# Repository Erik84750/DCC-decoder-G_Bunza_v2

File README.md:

# DCC-decoder-G_Bunza_v2
DCC++ decoder based on the work of G. Bunza

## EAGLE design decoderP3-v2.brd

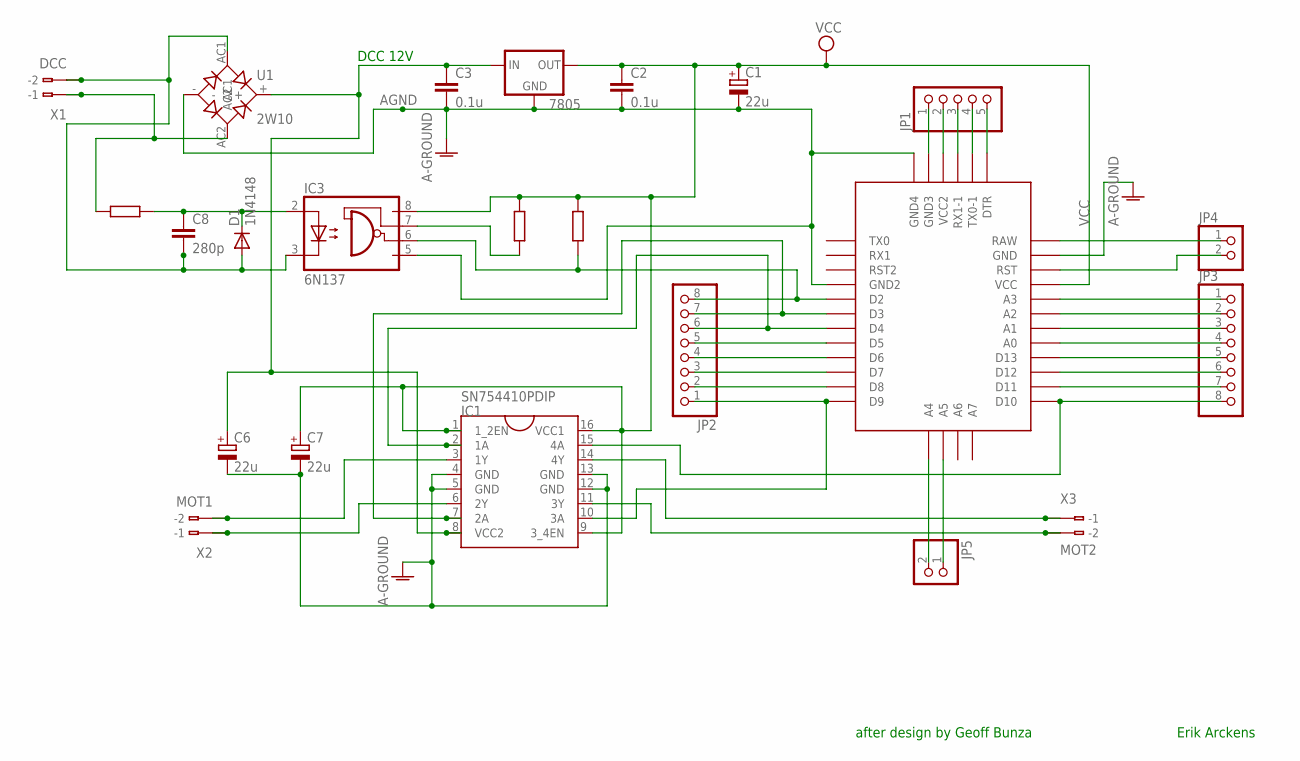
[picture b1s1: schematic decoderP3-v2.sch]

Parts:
7805: 78XXS
C1: 22u; ELCO-2.5MMLEAD
C2, C3: 0.1u; CERAMIC-CAP-C050-025X075
C6, C7: 22u; AVX-C
C8: 280p; CERAMIC-CAP-C050-025X075
D1: 1N4148; DO35-7-1N4148
IC1: SN754410PDIP; DIL16
IC2: ARDUINO Pro Mini; ARDUINO-PRO-MINI-FULL
IC3: 6N137; DIL08
JP1: 1X05
JP2, JP3: 1X08
JP4, JP5: 1X02
R12: 10k; 0207/2V_VERTICAL_1/4W_RESISTOR
R17: 5k; 0207/2V_VERTICAL_1/4W_RESISTOR
R18: 1.8k; 0207/2V_VERTICAL_1/4W_RESISTOR
U1: 2W10
X1: DCC; PCB-TERMINAL-2POLE-0.1-INCH
X2: MOT1; PCB-TERMINAL-2POLE-0.1-INCH
X3: MOT2; PCB-TERMINAL-2POLE-0.1-INCH

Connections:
AGND: 7805.GND, C1.-, C2.P$1, C3.P$1, C6.-, C7.-, IC1.4 (GND), IC1.5 (GND), IC1.12 (GND), IC1.13 (GND), IC2.GND, IC2.GND1 (GND2), IC2.GND2 (GND4), IC3.5 (GND), U1.-
unnamed: C8.P$1, D1.A, IC3.3 (C), U1.AC1, X1.A2 (-2), X1.B2 (B-2)
unnamed: IC2.D5, JP2.5
unnamed: IC2.D6, JP2.4
unnamed: 7805.IN, C3.P$2, C6.+, IC1.8 (VCC2), U1.+
unnamed: R18.1, U1.AC2, X1.A1 (-1), X1.B1 (B-1)
unnamed: IC1.2 (1A), IC2.D4, JP2.6
unnamed: IC2.D7, JP2.3
unnamed: IC1.3 (1Y), X2.A2 (-2), X2.B2 (B-2)
unnamed: IC1.6 (2Y), X2.A1 (-1), X2.B1 (B-1)
unnamed: IC1.11 (3Y), X3.A2 (-2), X3.B2 (B-2)
unnamed: IC1.10 (3A), IC2.D9, JP2.1
unnamed: IC3.7 (VE), R12.1
unnamed: IC1.7 (2A), IC2.D3, JP2.7
unnamed: IC2.D8, JP2.2
unnamed: IC2.A3, JP3.1
unnamed: IC1.15 (4A), IC2.D10, JP3.8
unnamed: IC1.14 (4Y), X3.A1 (-1), X3.B1 (B-1)
unnamed: IC2.A2, JP3.2
unnamed: IC2.A1, JP3.3
unnamed: IC2.D2, IC3.6 (VO), JP2.8, R17.1
unnamed: IC2.A0, JP3.4
unnamed: IC2.D13, JP3.5
unnamed: IC2.D12, JP3.6
unnamed: IC2.D11, JP3.7
unnamed: IC2.RAW, JP4.1
unnamed: IC2.RST, JP4.2
unnamed: IC2.GND3, JP1.1
unnamed: IC2.VCC1 (VCC2), JP1.2
unnamed: IC2.RX1-1, JP1.3
unnamed: IC2.TX0-1, JP1.4
unnamed: IC2.DTR, JP1.5
unnamed: IC2.A4, JP5.2
unnamed: IC2.A5, JP5.1
unnamed: C8.P$2, D1.C, IC3.2 (A), R18.2
VCC: 7805.OUT, C1.+, C2.P$2, C7.+, IC1.1 (1_2EN), IC1.9 (3_4EN), IC1.16 (VCC1), IC2.VCC, IC3.8 (VCC), R12.2, R17.2

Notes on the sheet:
Erik Arckens
after design by Geoff Bunza
DCC 12V

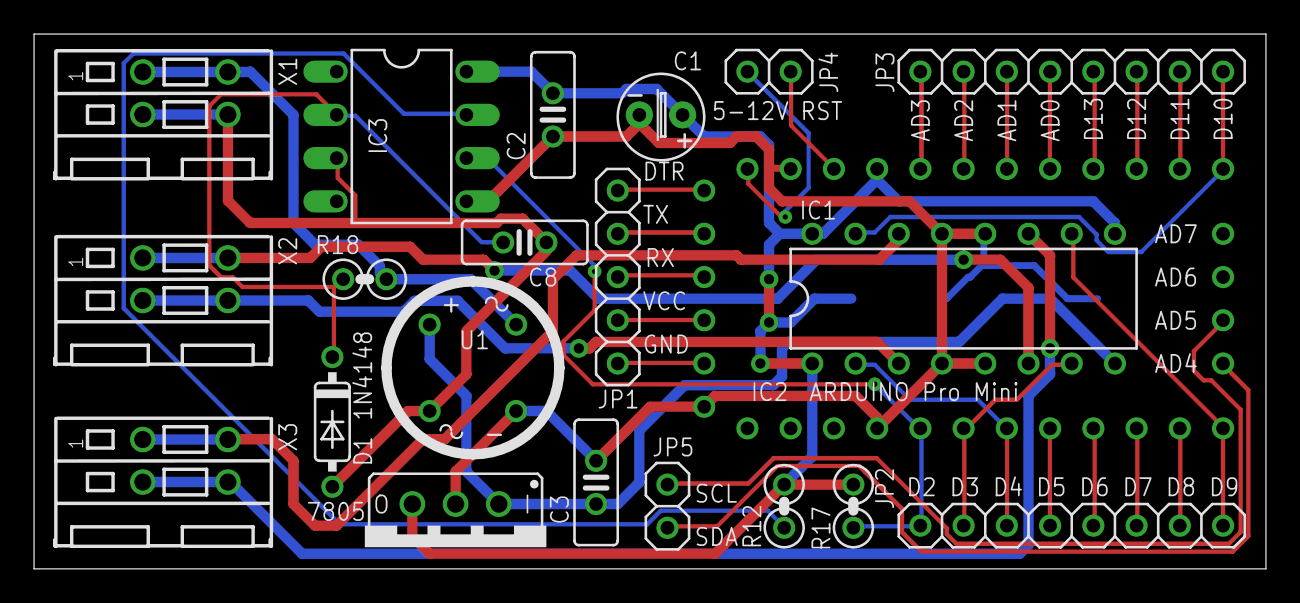
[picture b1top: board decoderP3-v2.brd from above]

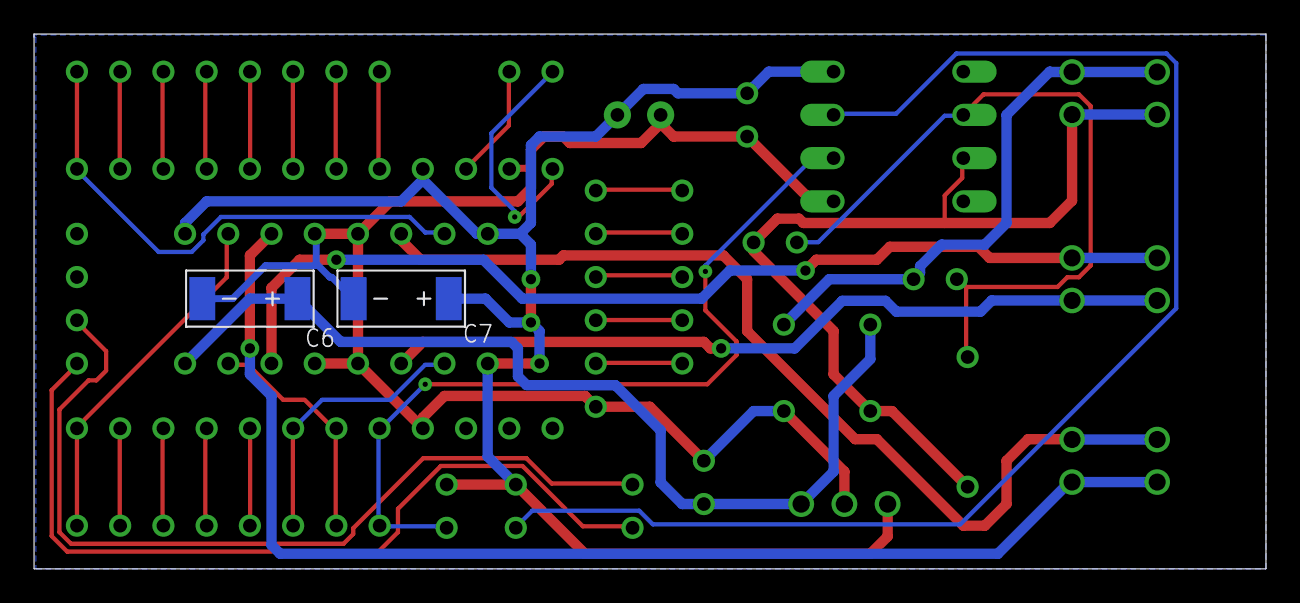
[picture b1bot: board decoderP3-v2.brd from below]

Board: 2 copper layers, 72.4 x 31.4 mm, 23 parts (2 on the bottom side), 36 nets.

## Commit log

2016-11-14 Add files via upload
    This project was started, based on the Geoff Bunza DCC++ decoder project documented on http://model-railroad-hobbyist.com/node/24316.
    I wanted to add extra connectors and adjust the layout for different component footprints.
